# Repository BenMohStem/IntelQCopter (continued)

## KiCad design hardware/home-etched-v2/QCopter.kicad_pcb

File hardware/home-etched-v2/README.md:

# Single-sided ESP32-S3 carrier PCB - revision 2

**Start with [the interactive assembly guide](output/assembly-guide.html).**
Open `QCopter.kicad_pro` in KiCad, then its PCB editor. This is a new routed project;
the previous connected reference and the user's original Documents project are preserved.

| Deliverable | File |
|---|---|
| Native KiCad project | [QCopter.kicad_pro](QCopter.kicad_pro) |
| PCB | [QCopter.kicad_pcb](QCopter.kicad_pcb) |
| Connected schematic, including every wire link | [QCopter.kicad_sch](QCopter.kicad_sch) |
| Three identical actual-size toner-transfer masks, no text | [Print PDF](output/etch-mask-3-copies-A4-1to1.pdf) |
| Component view and selectable wire endpoints | [Assembly guide](output/assembly-guide.html) |
| Drill coordinates | [drill-map.csv](output/drill-map.csv) |
| Native electrical result | [DRC](validation/native-drc.json), [graph check](verification.json) |

## Board and fabrication

- Board: **90 x 90 mm**, copper on the underside **B.Cu only**; no top tracks or vias.
- Signals: 0.6 mm tracks. Power/ground/BEC tracks: 1.0 mm. Copper clearance: 0.5 mm minimum.
- Module/header pads: 2.0 mm round copper, 1.1 mm drill. Wire links: 2.4 mm copper, 1.1 mm drill.
- Remote lidar: four 3.2 mm solder pads, 1.2 mm drills, 5.08 mm pitch.
- Four 3.2 mm mounting holes at (4,4), (86,4), (4,86), (86,86) mm. This is a carrier pattern;
  **it is not a measured F450 mounting pattern**. Use a suitable adapter/support.
- Large GND pour with **solid** pad connections. White holes are empty; no copper crosshairs.
- **W1-W27 are mandatory insulated wires**, placed on the component side and soldered underneath.
  They replace crossings that a one-face etch cannot make. There are 27 wires, not a second copper face.
  In particular W1/W2 also bridge ground sections: do not omit them because a pad looks surrounded by copper.
- Fit the ESP32 and all three sensor modules into **raised female sockets**. Keep wires flat,
  insulated and mechanically secured; verify **at least 3 mm free space above every wire**.
  Choose socket height from the actual underside parts; nominal 8.5 mm sockets are a starting point.
  The KiCad courtyards describe the sockets at carrier level; full module outlines remain on F.Fab.
  A flat wire under an elevated module occupies a different height. Direct flush-mounted modules are unsuitable.
- Keep the marked USB plug corridor clear and the antenna area free of added copper, wires and metal.
  The mask has no copper beneath the nominal antenna footprint. Keep motor wiring away from the compass/IMU.
- KiCad represents through-hole pads on both face layers, but **only B.Cu is etched**. Holes are manually
  drilled and unplated. Solder every pin on the underside. Do not interpret the file as a two-layer manufacturing order.

## Printing the mask

Use **Actual size / 100%**, A4, no Fit/Shrink, and disable any extra printer mirroring.
Black preserves copper. White is etched away or drilled out. The page contains only three masks.
The artwork uses component-side coordinates: printing it unchanged and placing the **toner face down
against the underside copper** makes the one required reflection. No further mirror operation is needed.
This orientation applies to the iron/toner-transfer process requested by the user.

The PDF's vectors were checked at exactly 72/25.4 points per mm, three copies, A4,
`PrintScaling=None`, zero text and 156 drill voids per copy. A printer can still introduce scale error:
before transfer, measure **22.86 mm between the ESP socket rows**, **53.34 mm from first to last pin**,
and **2.54 mm between adjacent module pins**. Place the real parts against the paper to verify fit and polarity.
The asymmetric antenna blank area and lidar pads help compare orientation with the assembly view.

## Power - one verified BEC

ESC motor/battery wires go to a separate power distribution board. **No 40 A path runs through this PCB.**
ESC J2-J5 have pin 1 GND, pin 2 that ESC's BEC output, pin 3 signal. Connector order is chosen here;
verify each ESC cable's actual order before connecting it.

All JP1-JP4 links are open initially. After measuring a regulated **5 V** BEC, fit **at most one** link:
JP1 selects ESC1, JP2 selects ESC2, etc. The other BEC red wires remain electrically separate.
An ESC's 40 A rating does not guarantee a BEC exists or that its voltage/current is suitable.
Remove **all** BEC links before USB power/programming. The DevKit's 5 V, 3.3 V and USB supply options
are mutually exclusive according to Espressif. The companion computer uses a separate power supply.

The chosen 5 V rail powers DevKit 5V and lidar. The DevKit's regulated 3V3 rail powers the sensors;
I2C/UART remain 3.3 V logic. Never connect 3S LiPo voltage directly to these rails.
R1/R2 are optional 4.7 kohm I2C pullups and **DNP initially**: module pullups already combine in parallel.
Verify actual module input limits, regulator output and I2C high levels; clone modules differ.

## Connector map, component side

| Part | Pins in order from pad 1 | ESP GPIO / detail |
|---|---|---|
| U2 MPU6050 GY-521, 8 pins | 3V3, GND, SCL, SDA, AUX_SDA, AUX_SCL, GND, INT | SCL8, SDA9, INT16; address 0x68 |
| U3 BMP280, 6 pins | 3V3, GND, SCL, SDA, 3V3, GND | CSB high selects I2C; SDO low selects 0x76 |
| U4 GY-271, 5 pins | 3V3, GND, SCL, SDA, DRDY | DRDY17; actual compass chip/address unverified |
| J1 remote lidar wires | 5V, GND, TX from lidar, RX to lidar | FC RX6, TX7; **not a factory cable color/order** |
| J2 ESC1 | GND, BEC1, signal | GPIO12 |
| J3 ESC2 | GND, BEC2, signal | GPIO1 |
| J4 ESC3 | GND, BEC3, signal | GPIO2 |
| J5 ESC4 | GND, BEC4, signal | GPIO14 |
| JP1-JP4 | corresponding BEC, FC_5V | Fit at most one; all removed for USB |
| J6 MPU auxiliary interface | 3V3, GND, AUX_SCL, AUX_SDA | Separate from the main host I2C bus |
| J7 companion UART | GND, FC TX, FC RX | GPIO5 to companion RX; GPIO4 from companion TX; 3.3 V only |

U1 is the **44-pin Espressif ESP32-S3-DevKitC-1 reference**, 22 pins per row,
2.54 mm pitch, rows 22.86 mm apart. Its pad numbers are header numbers, not GPIO numbers.
See the numbered assembly guide, native schematic and connections.json for all 44 pads.

## Mechanical assumptions and hardware acceptance

Nominal bodies: MPU6050 21.2 x 16.4 mm, BMP280 15.5 x 11.8 mm, GY-271 13.5 x 14.8 mm.
For sensors, the first dimension is along the pin row. The exact clone header-to-edge distance
and row centering are still assumptions. Refer to [the source-linked dimensions](module-dimensions.md).
The ESP body is 25.40 x 62.74 mm, with its last header pin 8.00 mm before the USB-end edge;
the antenna overhang is drawn separately. The actual purchased clone and cable housings must be checked.

Native checks show **0 DRC violations / 0 unconnected items**, 44 schematic components plus
4 mounting holes, 156 pads/holes, and all original logical nets connected through the fitted wires.
Voltage rails and BEC feeds remain distinct. These are CAD checks, **not a manufactured-board continuity test**.
After etching/drilling, inspect tracks and annuli, check 5V-to-GND and 3V3-to-GND for shorts, then
check each ground and connector end-to-end before inserting modules or connecting power.

The current bench firmware remains unchanged and has motor outputs disabled. This PCB does not
validate slow sensor drivers, Xbox, companion communications, flight control or a BEC under load.
Battery voltage/current sensing, cell monitoring and high-current distribution are not included in this carrier revision.

## Recheck and reproduce

From QCopter-Stepwise:

```powershell
.\qcopter.ps1 check-home-etched-pcb
```

This saves original KiCad DRC/netlist logs under `.local/home-etched-checks/` and performs
an independent native schematic/PCB comparison plus a graph check through every W link.
Original failed routing reports are retained in `validation/failed-trials/`.
The native board is authoritative; `route-model.json` is its routing input, not an acceptance test.
Tools live in `tools/hardware/`: build_home_etched_pcb.py, check_routed_pcb.py,
export_routed_geometry.py, make_routed_outputs.py and verify_home_etched_pcb.py.
The builder requires KiCad Python and a **new output directory**. PDF generation requires ReportLab/pypdf.
Use isolated dependencies; do not install them into KiCad's Python or the FC environment.

Primary references:
- [Espressif DevKit header/power guide](https://documentation.espressif.com/esp-dev-kits/en/latest/esp32s3/esp32-s3-devkitc-1/user_guide_v1.0.html)
- [Espressif mechanical drawing](https://dl.espressif.com/dl/DXF_ESP32-S3-DevKitC-1_V1_20210312CB.pdf)
- [Bosch BMP280 datasheet](https://www.bosch-sensortec.com/media/boschsensortec/downloads/datasheets/bst-bmp280-ds001.pdf)

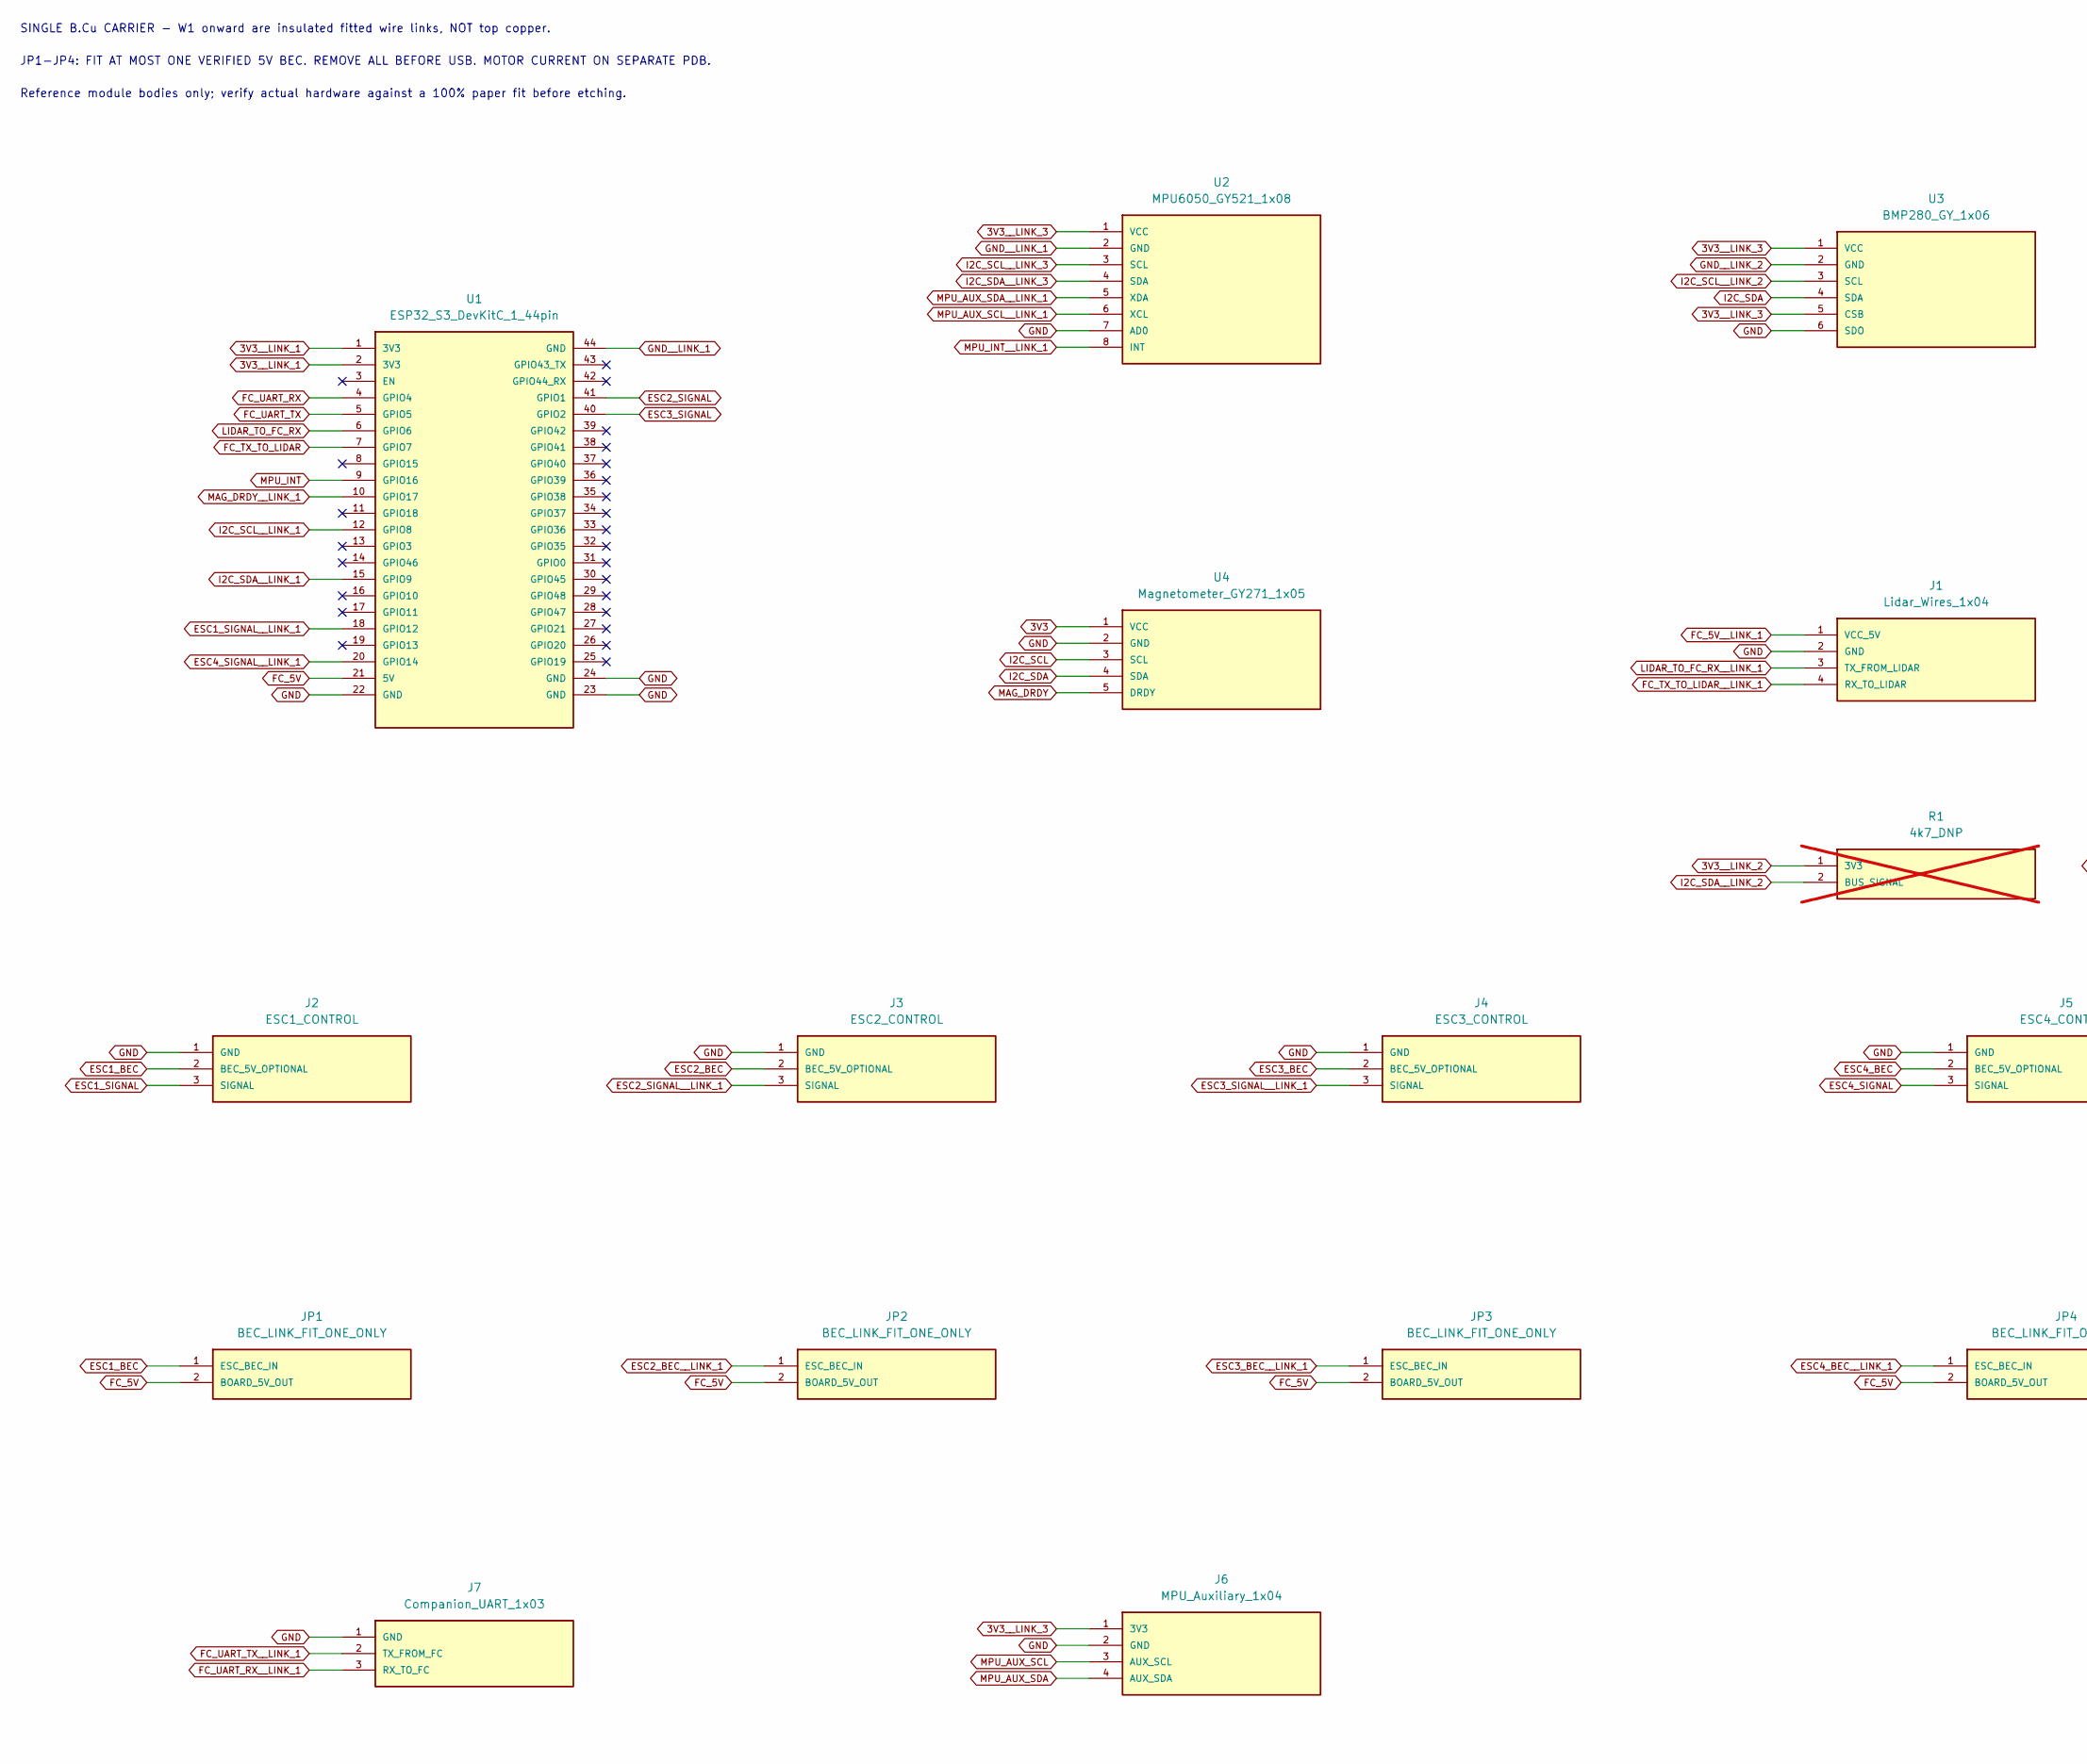
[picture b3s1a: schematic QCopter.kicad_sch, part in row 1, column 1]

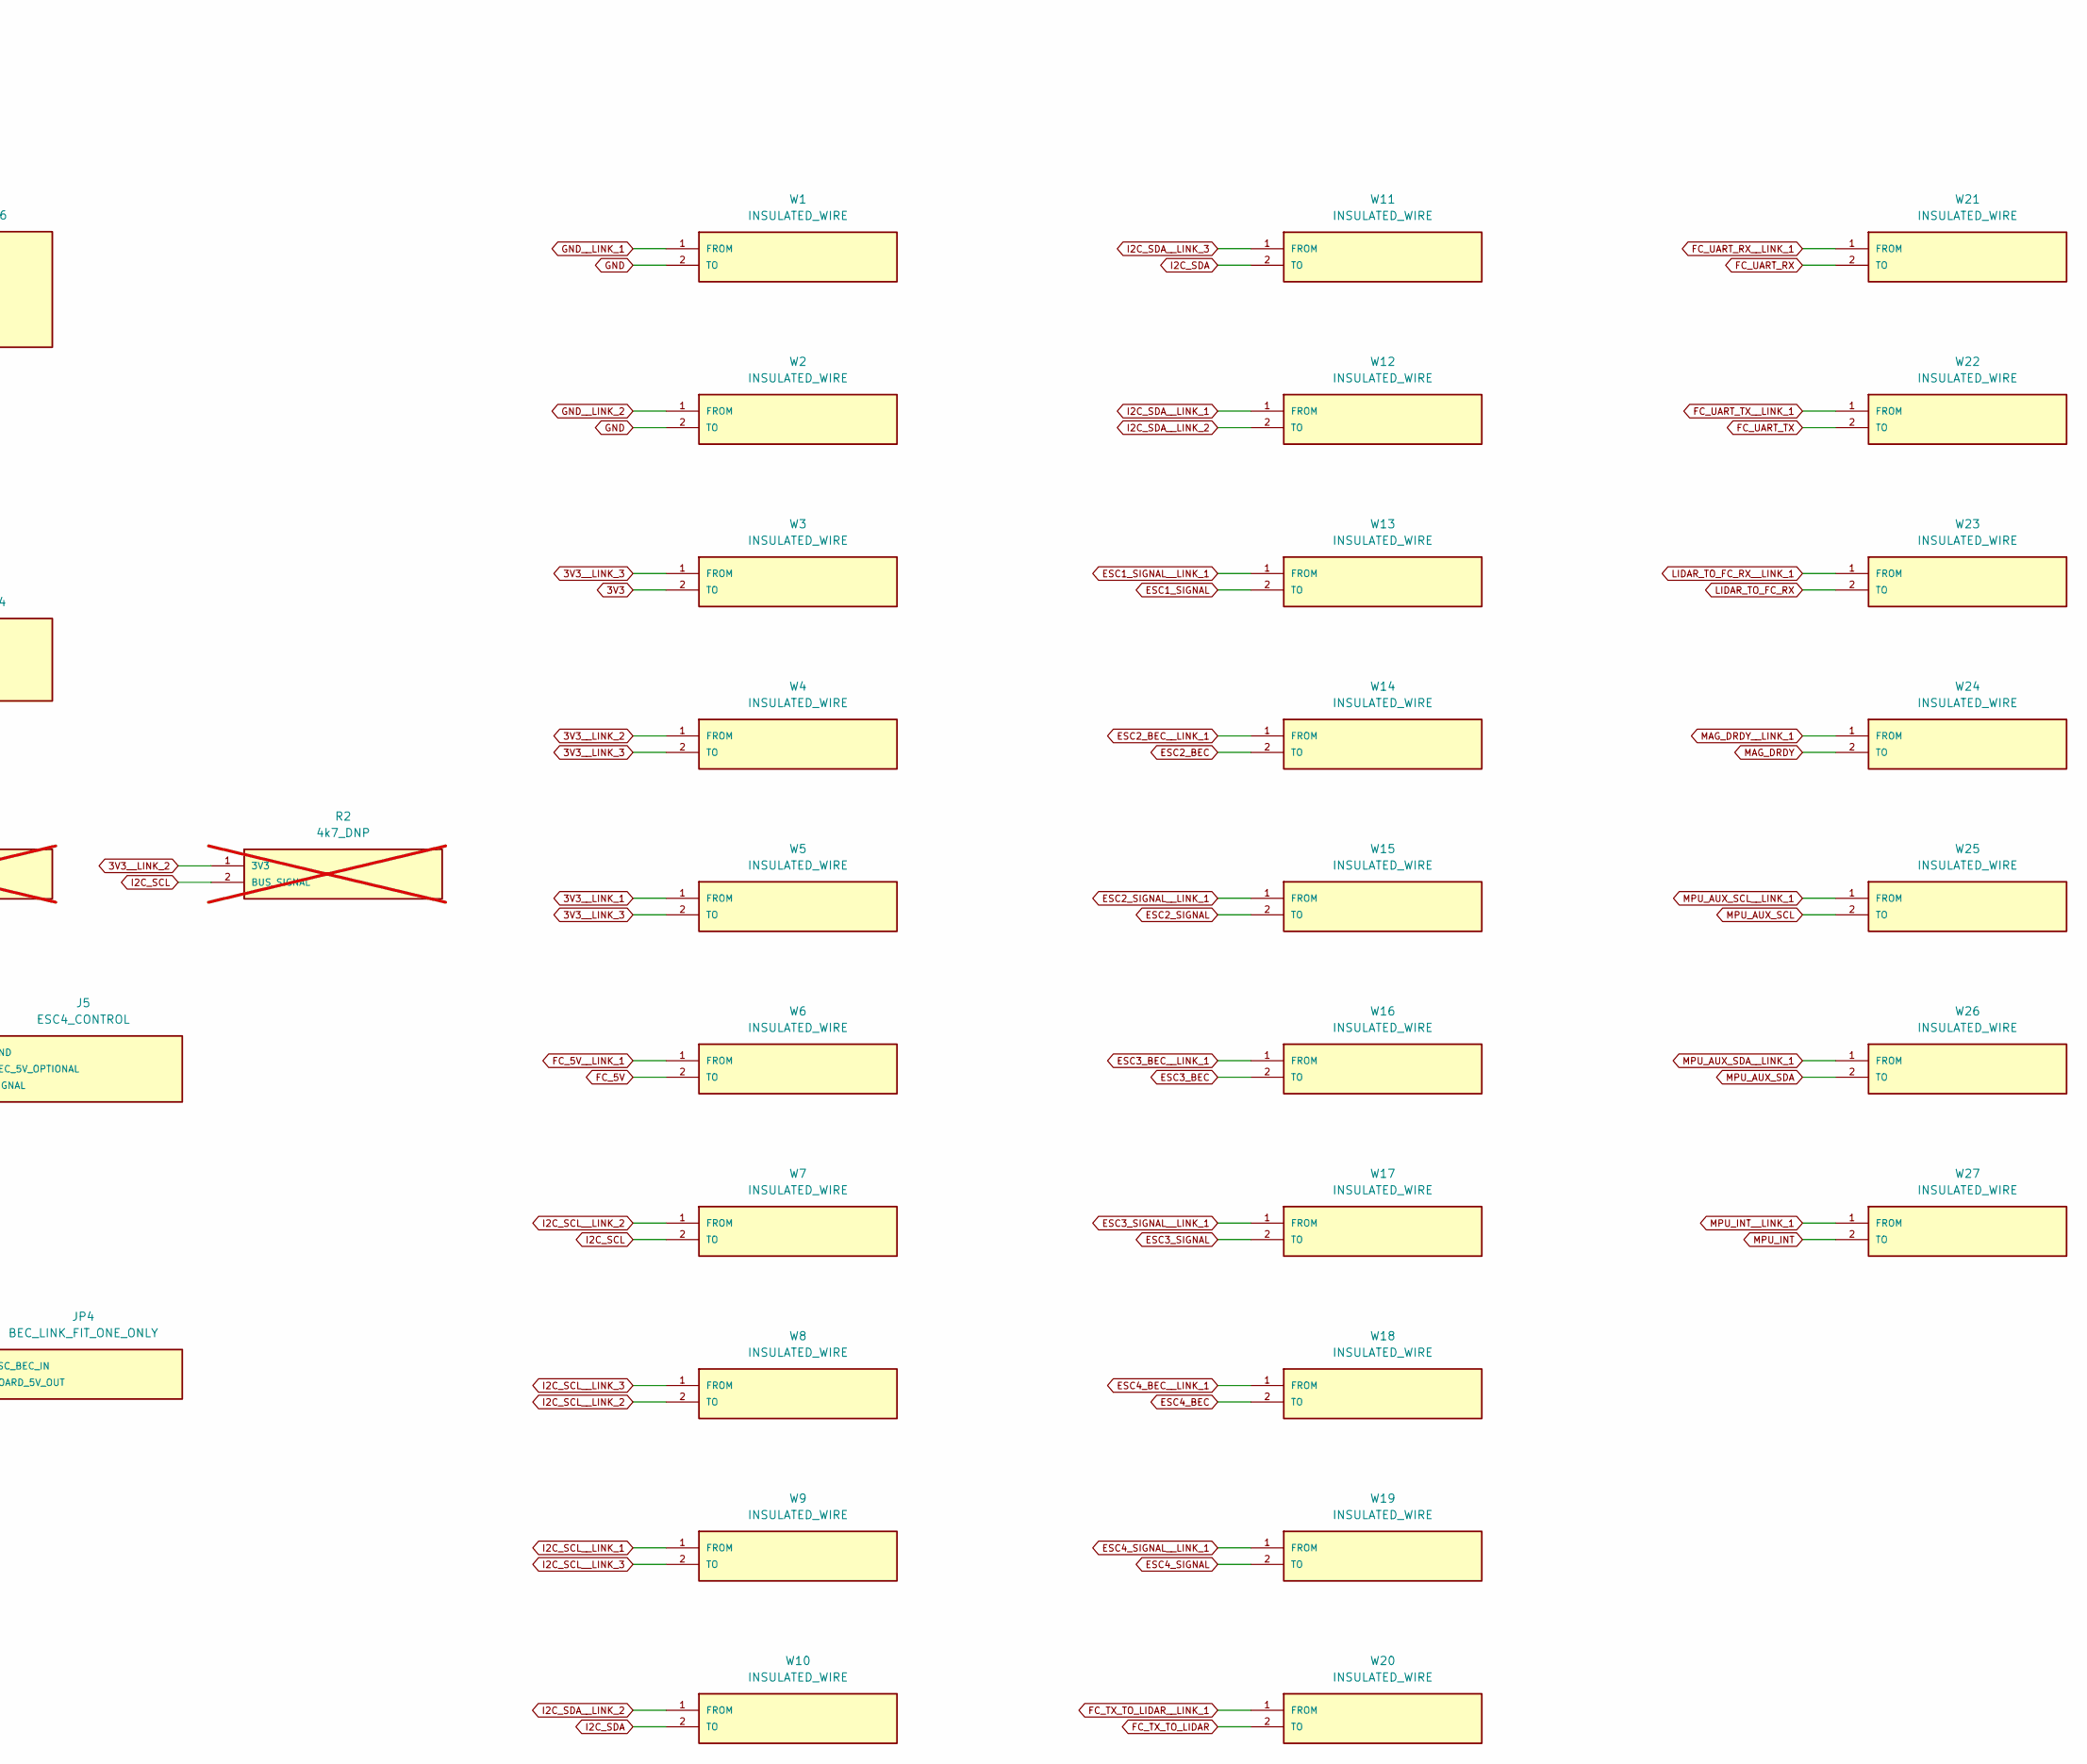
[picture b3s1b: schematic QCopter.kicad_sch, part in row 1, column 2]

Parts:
J1: Lidar_Wires_1x04
J2: ESC1_CONTROL; ESC_Servo_1x03
J3: ESC2_CONTROL; ESC_Servo_1x03
J4: ESC3_CONTROL; ESC_Servo_1x03
J5: ESC4_CONTROL; ESC_Servo_1x03
J6: MPU_Auxiliary_1x04
J7: Companion_UART_1x03
JP1, JP2, JP3, JP4: BEC_LINK_FIT_ONE_ONLY; BEC_Link_1x02
R1, R2: 4k7_DNP; Optional_Pullup_Axial_P10_16; not fitted
U1: ESP32_S3_DevKitC_1_44pin
U2: MPU6050_GY521_1x08
U3: BMP280_GY_1x06
U4: Magnetometer_GY271_1x05
W1: INSULATED_WIRE; Insulated_Link_W1
W2: INSULATED_WIRE; Insulated_Link_W2
W3: INSULATED_WIRE; Insulated_Link_W3
W4: INSULATED_WIRE; Insulated_Link_W4
W5: INSULATED_WIRE; Insulated_Link_W5
W6: INSULATED_WIRE; Insulated_Link_W6
W7: INSULATED_WIRE; Insulated_Link_W7
W8: INSULATED_WIRE; Insulated_Link_W8
W9: INSULATED_WIRE; Insulated_Link_W9
W10: INSULATED_WIRE; Insulated_Link_W10
W11: INSULATED_WIRE; Insulated_Link_W11
W12: INSULATED_WIRE; Insulated_Link_W12
W13: INSULATED_WIRE; Insulated_Link_W13
W14: INSULATED_WIRE; Insulated_Link_W14
W15: INSULATED_WIRE; Insulated_Link_W15
W16: INSULATED_WIRE; Insulated_Link_W16
W17: INSULATED_WIRE; Insulated_Link_W17
W18: INSULATED_WIRE; Insulated_Link_W18
W19: INSULATED_WIRE; Insulated_Link_W19
W20: INSULATED_WIRE; Insulated_Link_W20
W21: INSULATED_WIRE; Insulated_Link_W21
W22: INSULATED_WIRE; Insulated_Link_W22
W23: INSULATED_WIRE; Insulated_Link_W23
W24: INSULATED_WIRE; Insulated_Link_W24
W25: INSULATED_WIRE; Insulated_Link_W25
W26: INSULATED_WIRE; Insulated_Link_W26
W27: INSULATED_WIRE; Insulated_Link_W27

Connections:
3V3: U4.1 (VCC), W3.2 (TO)
3V3__LINK_1: U1.1 (3V3), U1.2 (3V3), W5.1 (FROM)
3V3__LINK_2: R1.1 (3V3), R2.1 (3V3), W4.1 (FROM)
3V3__LINK_3: J6.1 (3V3), U2.1 (VCC), U3.1 (VCC), U3.5 (CSB), W3.1 (FROM), W4.2 (TO), W5.2 (TO)
ESC1_BEC: J2.2 (BEC_5V_OPTIONAL), JP1.1 (ESC_BEC_IN)
ESC1_SIGNAL: J2.3 (SIGNAL), W13.2 (TO)
ESC1_SIGNAL__LINK_1: U1.18 (GPIO12), W13.1 (FROM)
ESC2_BEC: J3.2 (BEC_5V_OPTIONAL), W14.2 (TO)
ESC2_BEC__LINK_1: JP2.1 (ESC_BEC_IN), W14.1 (FROM)
ESC2_SIGNAL: U1.41 (GPIO1), W15.2 (TO)
ESC2_SIGNAL__LINK_1: J3.3 (SIGNAL), W15.1 (FROM)
ESC3_BEC: J4.2 (BEC_5V_OPTIONAL), W16.2 (TO)
ESC3_BEC__LINK_1: JP3.1 (ESC_BEC_IN), W16.1 (FROM)
ESC3_SIGNAL: U1.40 (GPIO2), W17.2 (TO)
ESC3_SIGNAL__LINK_1: J4.3 (SIGNAL), W17.1 (FROM)
ESC4_BEC: J5.2 (BEC_5V_OPTIONAL), W18.2 (TO)
ESC4_BEC__LINK_1: JP4.1 (ESC_BEC_IN), W18.1 (FROM)
ESC4_SIGNAL: J5.3 (SIGNAL), W19.2 (TO)
ESC4_SIGNAL__LINK_1: U1.20 (GPIO14), W19.1 (FROM)
FC_5V: JP1.2 (BOARD_5V_OUT), JP2.2 (BOARD_5V_OUT), JP3.2 (BOARD_5V_OUT), JP4.2 (BOARD_5V_OUT), U1.21 (5V), W6.2 (TO)
FC_5V__LINK_1: J1.1 (VCC_5V), W6.1 (FROM)
FC_TX_TO_LIDAR: U1.7 (GPIO7), W20.2 (TO)
FC_TX_TO_LIDAR__LINK_1: J1.4 (RX_TO_LIDAR), W20.1 (FROM)
FC_UART_RX: U1.4 (GPIO4), W21.2 (TO)
FC_UART_RX__LINK_1: J7.3 (RX_TO_FC), W21.1 (FROM)
FC_UART_TX: U1.5 (GPIO5), W22.2 (TO)
FC_UART_TX__LINK_1: J7.2 (TX_FROM_FC), W22.1 (FROM)
GND: J1.2 (GND), J2.1 (GND), J3.1 (GND), J4.1 (GND), J5.1 (GND), J6.2 (GND), J7.1 (GND), U1.22 (GND), U1.23 (GND), U1.24 (GND), U2.7 (AD0), U3.6 (SDO), U4.2 (GND), W1.2 (TO), W2.2 (TO)
GND__LINK_1: U1.44 (GND), U2.2 (GND), W1.1 (FROM)
GND__LINK_2: U3.2 (GND), W2.1 (FROM)
I2C_SCL: R2.2 (BUS_SIGNAL), U4.3 (SCL), W7.2 (TO)
I2C_SCL__LINK_1: U1.12 (GPIO8), W9.1 (FROM)
I2C_SCL__LINK_2: U3.3 (SCL), W7.1 (FROM), W8.2 (TO)
I2C_SCL__LINK_3: U2.3 (SCL), W8.1 (FROM), W9.2 (TO)
I2C_SDA: U3.4 (SDA), U4.4 (SDA), W10.2 (TO), W11.2 (TO)
I2C_SDA__LINK_1: U1.15 (GPIO9), W12.1 (FROM)
I2C_SDA__LINK_2: R1.2 (BUS_SIGNAL), W10.1 (FROM), W12.2 (TO)
I2C_SDA__LINK_3: U2.4 (SDA), W11.1 (FROM)
LIDAR_TO_FC_RX: U1.6 (GPIO6), W23.2 (TO)
LIDAR_TO_FC_RX__LINK_1: J1.3 (TX_FROM_LIDAR), W23.1 (FROM)
MAG_DRDY: U4.5 (DRDY), W24.2 (TO)
MAG_DRDY__LINK_1: U1.10 (GPIO17), W24.1 (FROM)
MPU_AUX_SCL: J6.3 (AUX_SCL), W25.2 (TO)
MPU_AUX_SCL__LINK_1: U2.6 (XCL), W25.1 (FROM)
MPU_AUX_SDA: J6.4 (AUX_SDA), W26.2 (TO)
MPU_AUX_SDA__LINK_1: U2.5 (XDA), W26.1 (FROM)
MPU_INT: U1.9 (GPIO16), W27.2 (TO)
MPU_INT__LINK_1: U2.8 (INT), W27.1 (FROM)

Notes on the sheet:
SINGLE B.Cu CARRIER - W1 onward are insulated fitted wire links, NOT top copper.
JP1-JP4: FIT AT MOST ONE VERIFIED 5V BEC. REMOVE ALL BEFORE USB. MOTOR CURRENT ON SEPARATE PDB.
Reference module bodies only; verify actual hardware against a 100% paper fit before etching.

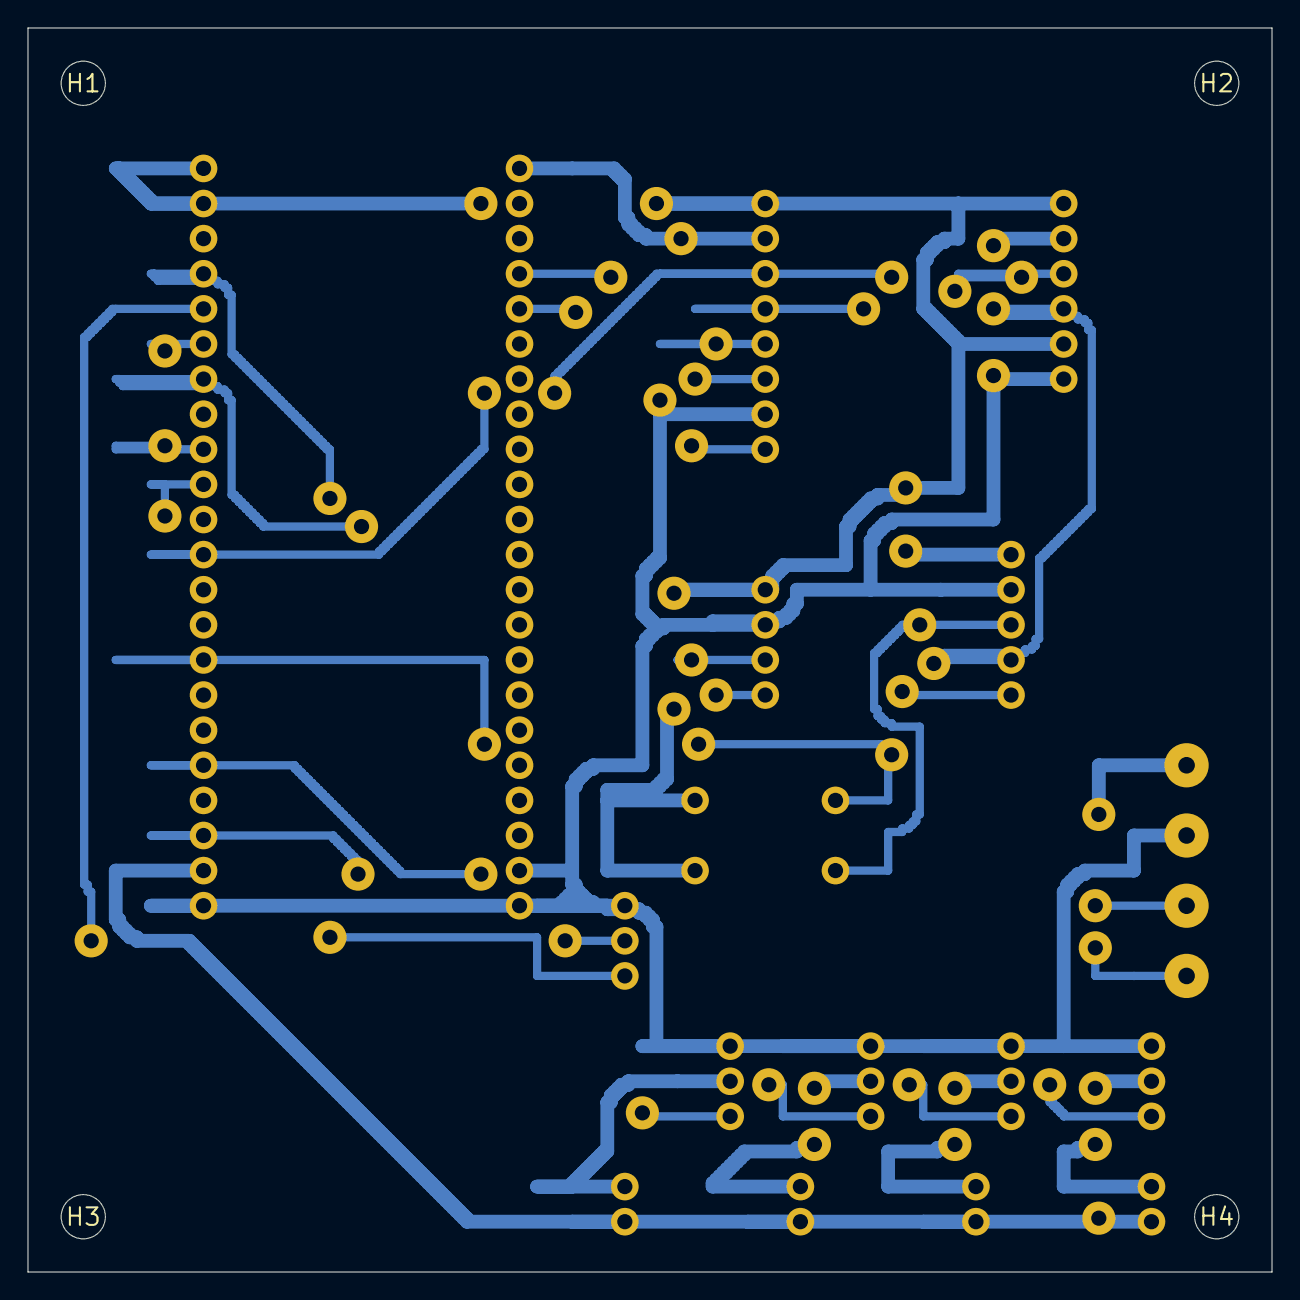
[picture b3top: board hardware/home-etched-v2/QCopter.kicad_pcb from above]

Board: 2 copper layers, 90.0 x 90.0 mm, 48 parts (0 on the bottom side), 48 nets.

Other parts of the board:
H1, H2, H3, H4: M3_CLEARANCE_NO_FRAME_PATTERN

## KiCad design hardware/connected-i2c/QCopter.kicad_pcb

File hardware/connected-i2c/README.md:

# Connected I2C reference: all current modules and spare interfaces

Open **QCopter.kicad_pro in this folder**. The schematic is connected through named
nets. The PCB has the same nets assigned to pads and shows airwires; it has **no
copper routes, board outline or ground pour**. Arrange and route it yourself.
This separate project preserves your existing open palette/layout.

## Sensor choice

Keep MPU6050, BMP280 and GY-271 on **I2C**, SDA GPIO9 and SCL GPIO8. BMP280 can use
SPI, but its low sample rate does not justify extra wires here; SPI does not
improve its pressure measurement accuracy. A shared-bus timing check is still
required when slow sensors are integrated into the 1 kHz acquisition firmware.
The MPU6050 and HMC5883L are I2C devices; do not mistake the SPI-capable MPU6000
for the MPU6050.

The physical interface is prepared. The current sensor-test firmware remains
MPU6050-only; this project does not implement new drivers, PID or ROS navigation.

## Connections

| Device | Power | Signals and extra pins |
|---|---|---|
| U2 MPU6050 | 3V3 / GND | SCL GPIO8, SDA GPIO9, INT GPIO16, AD0 GND; XDA/XCL to J6 auxiliary header |
| U3 BMP280 | 3V3 / GND | SCL GPIO8, SDA GPIO9; CSB to 3V3, SDO to GND: I2C address 0x76 |
| U4 GY-271 | 3V3 / GND | SCL GPIO8, SDA GPIO9, DRDY GPIO17 |
| J1 remote lidar | FC_5V / GND | Sensor TX to FC RX GPIO6; sensor RX from FC TX GPIO7 |
| J2 ESC1 | GND; own BEC net | Signal GPIO12; BEC through JP1 only |
| J3 ESC2 | GND; own BEC net | Signal GPIO1; BEC through JP2 only |
| J4 ESC3 | GND; own BEC net | Signal GPIO2; BEC through JP3 only |
| J5 ESC4 | GND; own BEC net | Signal GPIO14; BEC through JP4 only |
| J6 MPU auxiliary | 3V3 / GND | Pin3 AUX SCL from MPU XCL; pin4 AUX SDA from MPU XDA; separate from main I2C bus |
| J7 companion UART | GND, no power pin | Pin2 FC TX GPIO5 to computer RX; pin3 FC RX GPIO4 from computer TX |

J1 carrier wire order remains: 1 regulated 5 V, 2 GND, 3 TX_FROM_LIDAR, 4 RX_TO_LIDAR.
This is not a claim about the lidar's original cable order; identify wires by signal.
J7 requires **3.3 V UART logic**, not RS-232 or 5 V serial. Verify your companion
carrier's actual UART level and power it separately. The FC can operate without
the companion; its future serial driver must not be a dependency for manual flight.
UART and interrupt wiring do not mean those firmware interfaces are already tested.

Unused DevKit GPIOs remain accessible on its existing headers. Their schematic
no-connect markers mean "unused in this design", not that you physically lose
access. Every sensor/connector pin has a defined connection. J6 exposes the
MPU auxiliary bus rather than wrongly joining it to the host I2C bus.

## Power selection

**JP1-JP4 are removable two-pin links. Fit at most ONE**, and only for an ESC that
has a verified regulated **5 V BEC output**. A 40 A rating does not establish the
presence, voltage or capacity of a BEC. All four BEC wires reach separate link
inputs; the outputs reach FC_5V. They are not joined unless someone fits multiple
links. All links are initially open; the diagram does not magically select a source.

FC_5V powers the DevKit 5V pin and lidar. The DevKit regulator supplies sensor 3V3.
All ground references are connected. The high-current ESC battery/motor wiring
stays on a separate rated power distribution board, not through these connectors.
Remove **all BEC links before USB powering/programming**, per the reference
DevKit's mutually exclusive supply guidance. Voltage must be measured before use.

R1/R2 are optional **4.7k I2C pull-up footprints, DNP initially**. Modules may already
contain pullups; assess their combined resistance/rise time before fitting more.
All I2C pullups must go to 3V3. Generic passive symbols are interface placeholders;
their ERC result alone is not proof of a valid power architecture or correct assembly.

## Validation and use

The independent native netlist/PCB check verifies 17 components, 98 pad numbers,
all assigned nets, UART directions, I2C sharing, BMP straps, GPIO allocation and
separate BEC feeds. It cannot validate clone identities, physical fit, BEC output,
power noise, bus timing or completed copper routing. Those remain real tests.

From the Stepwise software checkout:

```powershell
.\qcopter.ps1 check-connected-pcb
```

In PCB Editor, enable F.Fab/F.CrtYd to see module bodies. Press M/R to place parts,
route the bottom copper for your single-sided process, and run DRC after routing.
Existing sensor body dimensions remain nominal references with assumed header
offsets; see module-dimensions.md. No physical motor arming is enabled.

References: [Bosch BMP280 interface selection](https://www.bosch-sensortec.com/media/boschsensortec/downloads/datasheets/bst-bmp280-ds001.pdf),
[Espressif DevKit power and headers](https://docs.espressif.com/projects/esp-dev-kits/en/latest/esp32s3/esp32-s3-devkitc-1/user_guide_v1.0.html),
[Hobbywing BEC backfeed guidance](https://support.hobbywingdirect.com/hc/en-us/articles/19157002618131-Using-a-Servo-Tester-to-operate-your-Electronic-Speed-Control).

[Original native connection-check output](validation.log) and [reviewed DRC findings](DRC-summary.json) are retained. DRC currently reports the missing outline and 52 unrouted items; no copper shorts/clearance violations were reported for this unrouted reference.

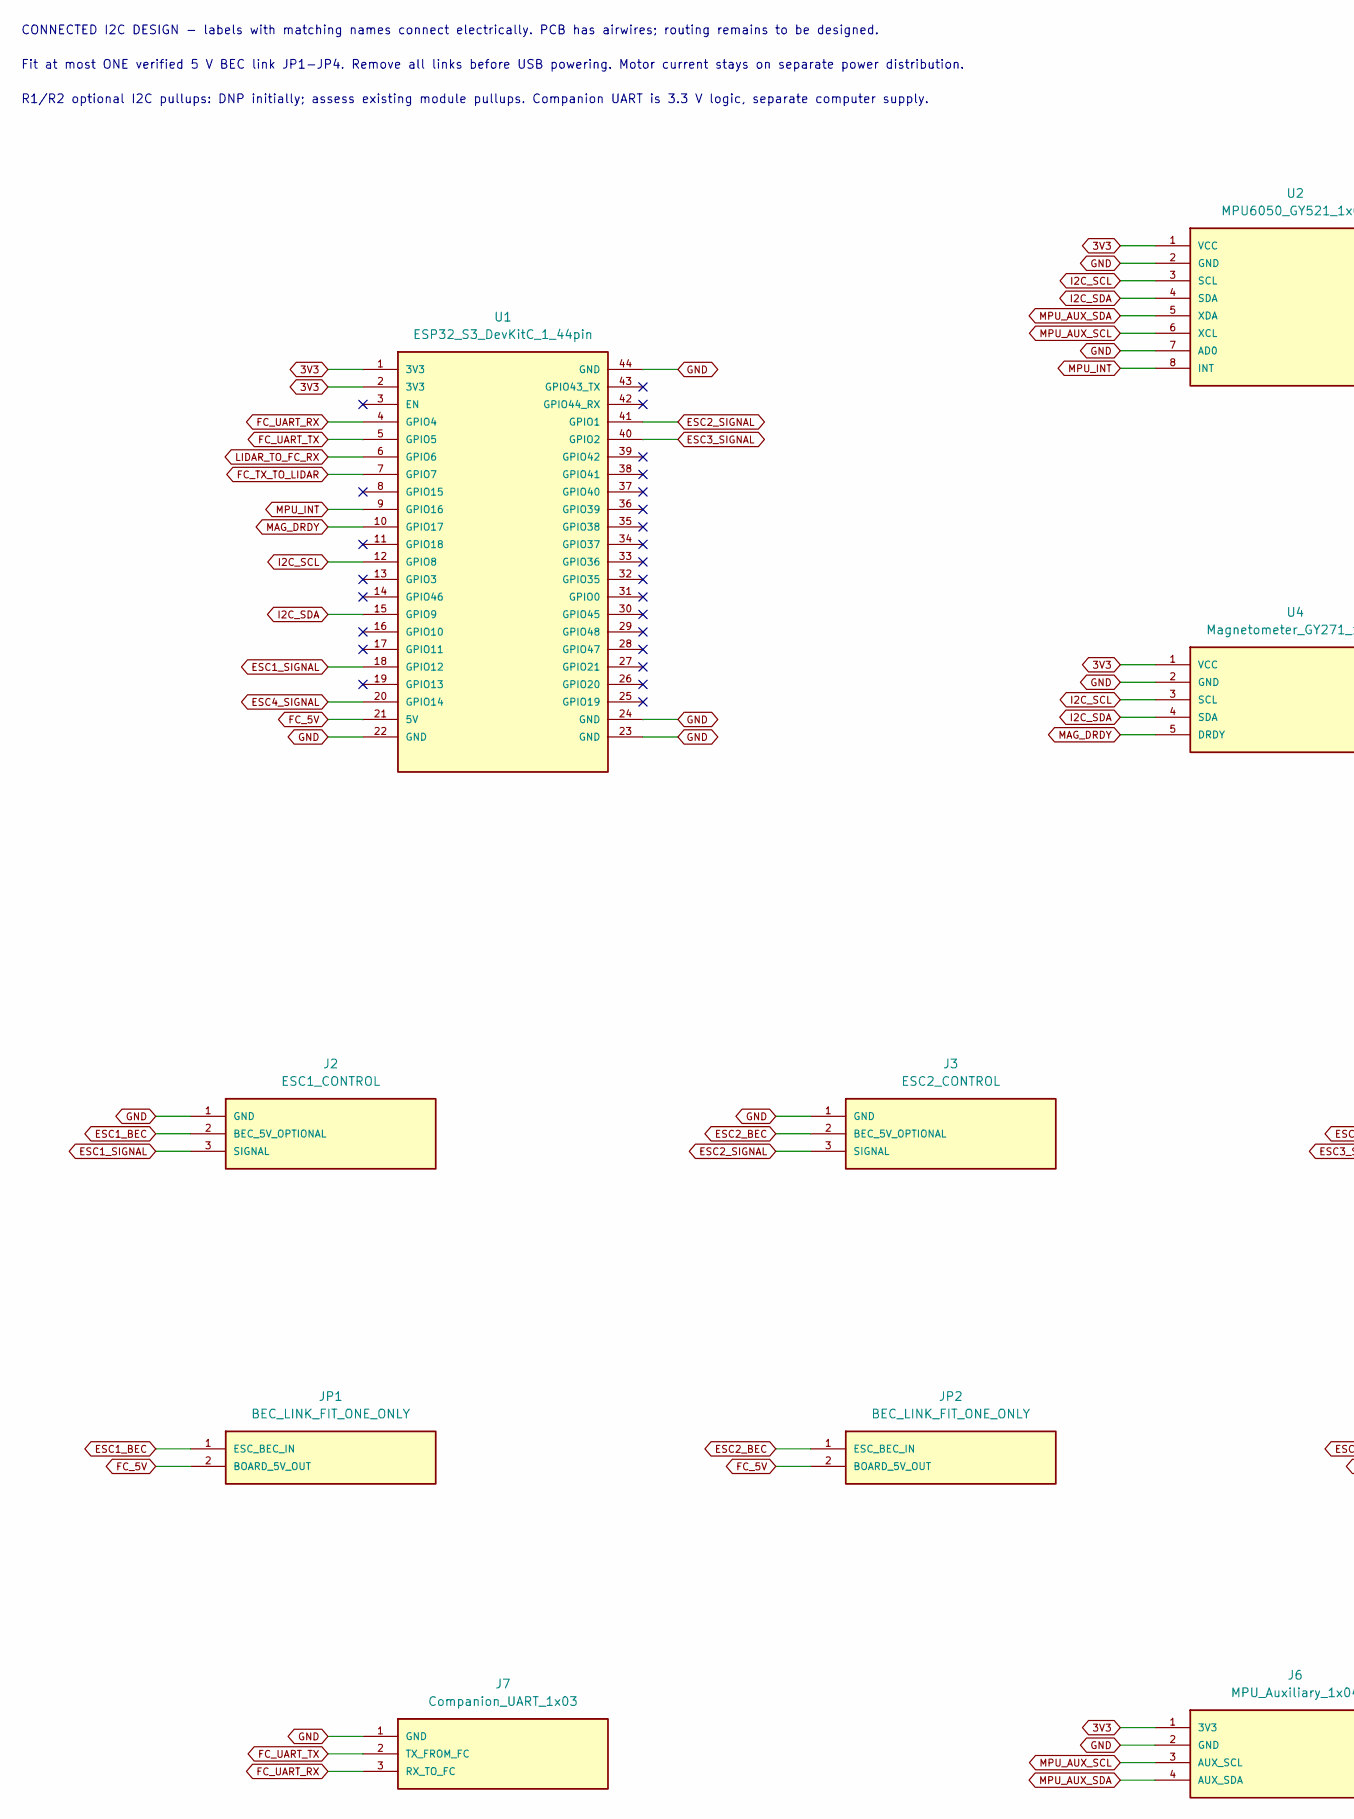
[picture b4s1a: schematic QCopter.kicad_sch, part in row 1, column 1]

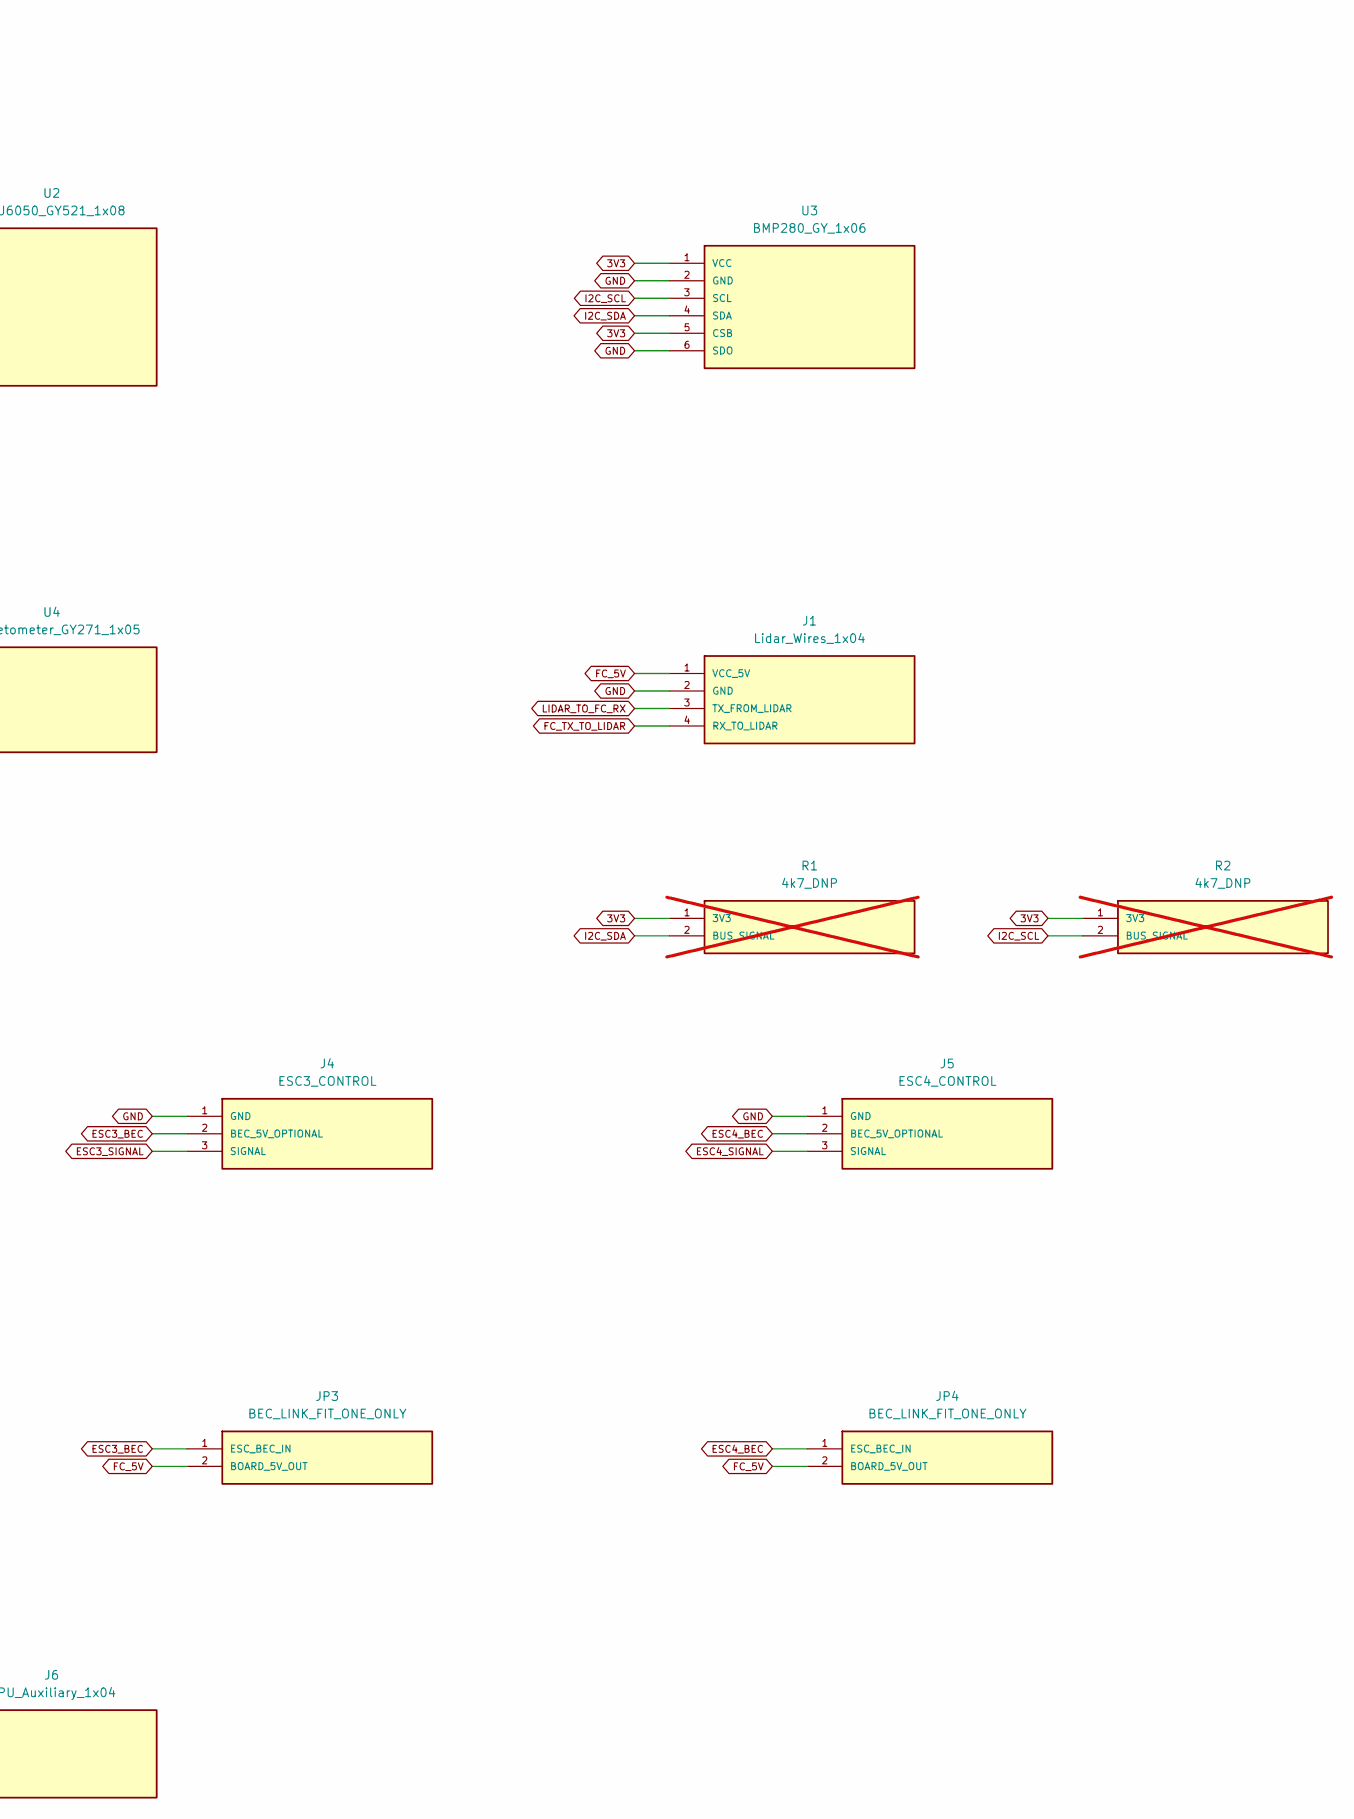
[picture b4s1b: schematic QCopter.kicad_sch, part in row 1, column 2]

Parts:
J1: Lidar_Wires_1x04
J2: ESC1_CONTROL; ESC_Servo_1x03
J3: ESC2_CONTROL; ESC_Servo_1x03
J4: ESC3_CONTROL; ESC_Servo_1x03
J5: ESC4_CONTROL; ESC_Servo_1x03
J6: MPU_Auxiliary_1x04
J7: Companion_UART_1x03
JP1, JP2, JP3, JP4: BEC_LINK_FIT_ONE_ONLY; BEC_Link_1x02
R1, R2: 4k7_DNP; Optional_Pullup_Axial_P10_16; not fitted
U1: ESP32_S3_DevKitC_1_44pin
U2: MPU6050_GY521_1x08
U3: BMP280_GY_1x06
U4: Magnetometer_GY271_1x05

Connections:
3V3: J6.1 (3V3), R1.1 (3V3), R2.1 (3V3), U1.1 (3V3), U1.2 (3V3), U2.1 (VCC), U3.1 (VCC), U3.5 (CSB), U4.1 (VCC)
ESC1_BEC: J2.2 (BEC_5V_OPTIONAL), JP1.1 (ESC_BEC_IN)
ESC1_SIGNAL: J2.3 (SIGNAL), U1.18 (GPIO12)
ESC2_BEC: J3.2 (BEC_5V_OPTIONAL), JP2.1 (ESC_BEC_IN)
ESC2_SIGNAL: J3.3 (SIGNAL), U1.41 (GPIO1)
ESC3_BEC: J4.2 (BEC_5V_OPTIONAL), JP3.1 (ESC_BEC_IN)
ESC3_SIGNAL: J4.3 (SIGNAL), U1.40 (GPIO2)
ESC4_BEC: J5.2 (BEC_5V_OPTIONAL), JP4.1 (ESC_BEC_IN)
ESC4_SIGNAL: J5.3 (SIGNAL), U1.20 (GPIO14)
FC_5V: J1.1 (VCC_5V), JP1.2 (BOARD_5V_OUT), JP2.2 (BOARD_5V_OUT), JP3.2 (BOARD_5V_OUT), JP4.2 (BOARD_5V_OUT), U1.21 (5V)
FC_TX_TO_LIDAR: J1.4 (RX_TO_LIDAR), U1.7 (GPIO7)
FC_UART_RX: J7.3 (RX_TO_FC), U1.4 (GPIO4)
FC_UART_TX: J7.2 (TX_FROM_FC), U1.5 (GPIO5)
GND: J1.2 (GND), J2.1 (GND), J3.1 (GND), J4.1 (GND), J5.1 (GND), J6.2 (GND), J7.1 (GND), U1.22 (GND), U1.23 (GND), U1.24 (GND), U1.44 (GND), U2.2 (GND), U2.7 (AD0), U3.2 (GND), U3.6 (SDO), U4.2 (GND)
I2C_SCL: R2.2 (BUS_SIGNAL), U1.12 (GPIO8), U2.3 (SCL), U3.3 (SCL), U4.3 (SCL)
I2C_SDA: R1.2 (BUS_SIGNAL), U1.15 (GPIO9), U2.4 (SDA), U3.4 (SDA), U4.4 (SDA)
LIDAR_TO_FC_RX: J1.3 (TX_FROM_LIDAR), U1.6 (GPIO6)
MAG_DRDY: U1.10 (GPIO17), U4.5 (DRDY)
MPU_AUX_SCL: J6.3 (AUX_SCL), U2.6 (XCL)
MPU_AUX_SDA: J6.4 (AUX_SDA), U2.5 (XDA)
MPU_INT: U1.9 (GPIO16), U2.8 (INT)

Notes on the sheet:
CONNECTED I2C DESIGN - labels with matching names connect electrically. PCB has airwires; routing remains to be designed.
Fit at most ONE verified 5 V BEC link JP1-JP4. Remove all links before USB powering. Motor current stays on separate power distribution.
R1/R2 optional I2C pullups: DNP initially; assess existing module pullups. Companion UART is 3.3 V logic, separate computer supply.

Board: 2 copper layers, 17 parts (0 on the bottom side), 21 nets, no tracks yet.
